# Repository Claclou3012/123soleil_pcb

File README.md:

# 1, 2, 3 Soleil — Version électronique

Réinterprétation électronique du jeu "1, 2, 3 Soleil" : trois stations équipées de capteurs de mouvement surveillent chaque joueur pendant la phase "Soleil" (silence), une LED RGB par joueur indique s'il est encore en jeu ou éliminé, le tout accompagné de musique et affiché sur un écran OLED.

## Principe du jeu

1. **Phase verte** : la musique joue, une LED au centre est allumée en vert, les joueurs peuvent avancer.
2. **Phase rouge** : la musique s'arrête, les 3 capteurs à ultrasons mesurent la distance de chaque joueur. Tout mouvement détecté élimine le joueur (sa LED passe au rouge).
3. Le cycle se répète jusqu'à ce qu'il ne reste plus qu'un joueur.

## Architecture électronique

```
Batterie LiPo ──> Verrouillage (S1 + Q2) ──> XIAO ESP32-S3
                                                   ├── Écran OLED (I2C) : round / joueurs restants
                                                   ├── Chaîne de 4 LED RGB adressables (3 joueurs + feu central)
                                                   ├── Haut-parleur (piloté par Q1) : musique / bruitages
                                                   └── 3x capteur HC-SR04 (Trig commun, Echo individuel avec pont diviseur)
```

### Points techniques clés
- **Double plan de masse** : une masse réelle (batterie, toujours active) et une masse commutée (périphériques, coupée par Q2 en veille), afin de permettre un allumage/extinction par simple pression sur un bouton, avec verrouillage électronique maintenu par le microcontrôleur.
- **Pont diviseur de tension** sur chaque ligne Echo, pour adapter le signal du HC-SR04 aux entrées 3,3V du XIAO.
- **Chaîne de LED adressables** pilotée depuis une seule broche du microcontrôleur.

## Liste des composants principaux

| Réf | Composant | Rôle |
|---|---|---|
| U1 | XIAO ESP32-S3 | Microcontrôleur |
| J1 | Écran OLED SSD1306 (I2C) | Affichage du jeu |
| U2, U3, U4 | HC-SR04 | Capteurs de mouvement (un par joueur) |
| D1-D3 | LED RGB adressable | Une par joueur |
| D4 | LED RGB adressable | Feu central (rouge/vert) |
| Q1 | NMOS | Pilotage du haut-parleur |
| Q2 | NMOS | Interrupteur à verrouillage (marche/arrêt) |
| S1 | Bouton poussoir | Marche / démarrage |
| LS1 | Haut-parleur | Musique et bruitages |
| J2 | Connecteur JST batterie | Alimentation LiPo |

La liste complète des composants (résistances, condensateurs, diodes) est disponible dans le fichier de schéma.

## Fichiers du projet

- `123Soleil.kicad_pro` — fichier projet KiCad
- `123Soleil.kicad_sch` — schéma électronique
- `123Soleil.kicad_pcb` — circuit imprimé (2 couches, plan de masse séparé sur chaque face)
- `ibom.html` 

## Images

### Schéma électronique

### PCB (vue 2D)

### Rendu 3D
### Recto

### Verso

## Fabrication et assemblage

- PCB 2 couches, plan de masse réelle en face arrière, plan de masse commutée en face avant.
- Plusieurs composants (XIAO, écran OLED, capteurs HC-SR04) sont montés sur supports de broches (sockets) plutôt que soudés directement, pour faciliter le remplacement.
- Point d'assemblage important : la broche VBAT du XIAO est une pastille sous le module, non accessible via les supports — un fil doit être soudé directement dessus avant d'enficher le module.

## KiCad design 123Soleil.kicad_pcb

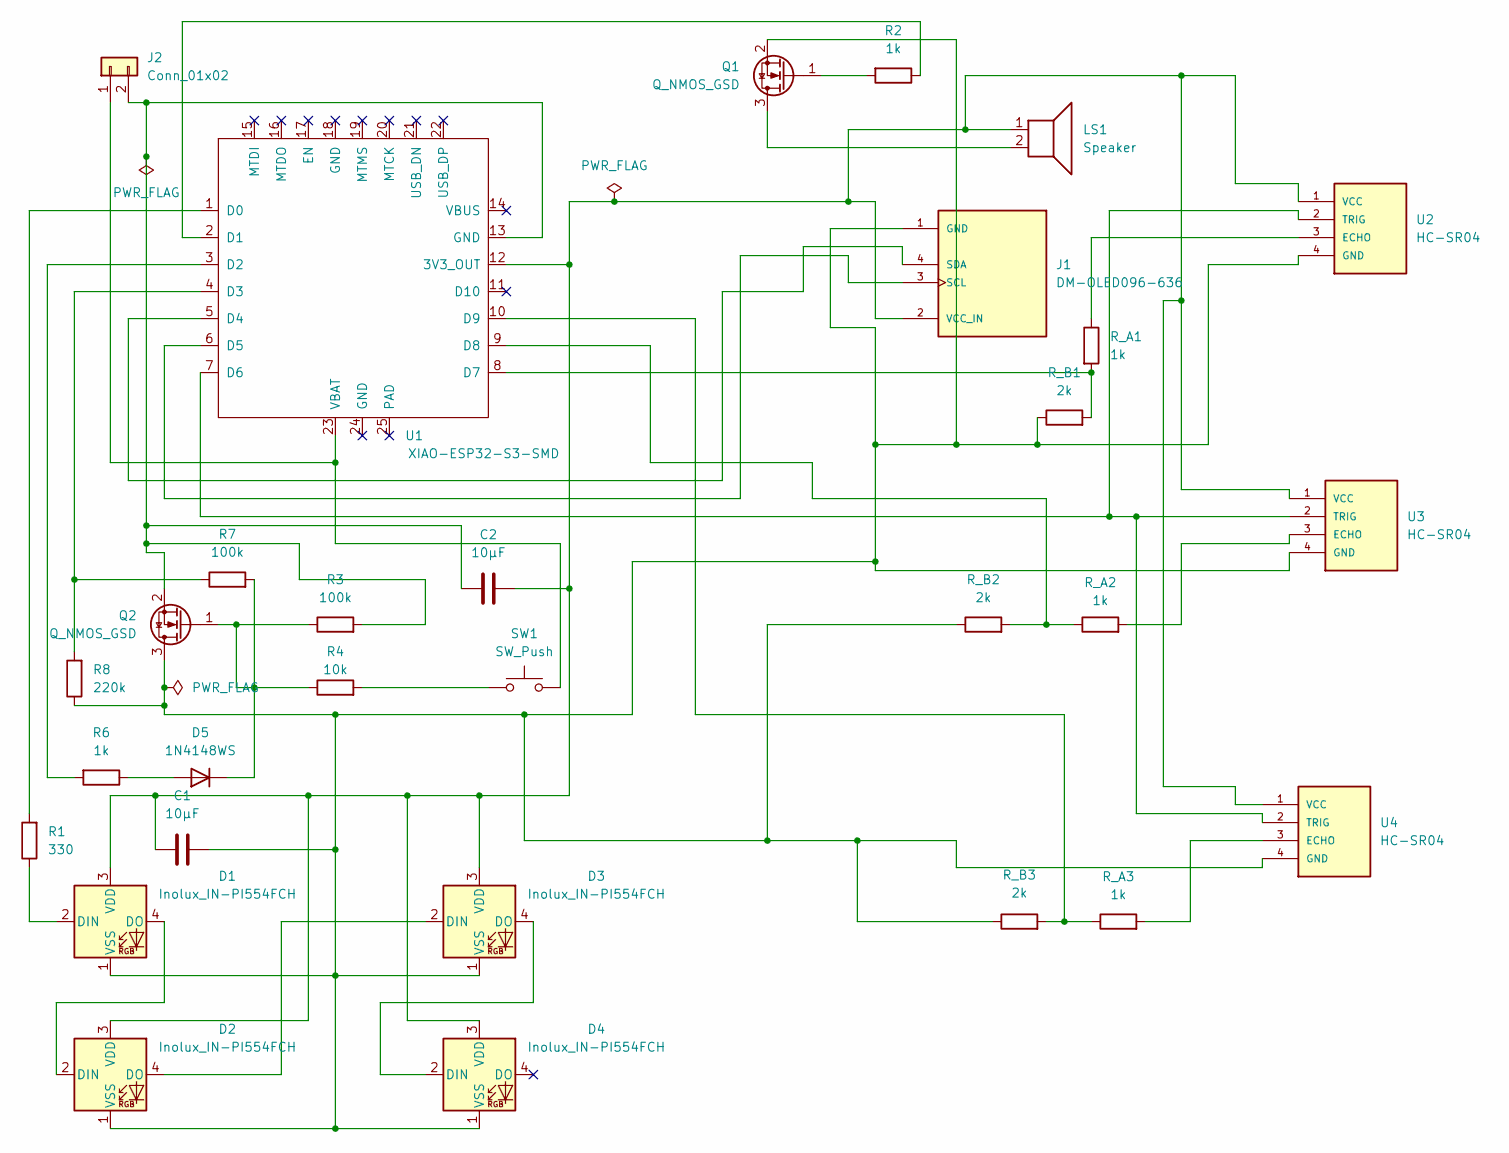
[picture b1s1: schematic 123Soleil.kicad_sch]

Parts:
C1, C2: 10µF; C_0805_2012Metric_Pad1.18x1.45mm_HandSolder
D1, D2, D3, D4: Inolux_IN-PI554FCH; LED_Inolux_IN-PI554FCH_PLCC4_5.0x5.0mm_P3.2mm
D5: 1N4148WS; D_SOD-323
J1: DM-OLED096-636; MODULE_DM-OLED096-636; PARTREV 2018-09-10
J2: Conn_01x02; JST_PH_S2B-PH-K_1x02_P2.00mm_Horizontal
LS1: Speaker; Speaker_CUI_CMR-1206S-67
Q1, Q2: Q_NMOS_GSD; SOT-23-3
R1: 330; R_0805_2012Metric_Pad1.20x1.40mm_HandSolder
R2, R6: 1k; R_0805_2012Metric_Pad1.20x1.40mm_HandSolder
R3, R7: 100k; R_0805_2012Metric_Pad1.20x1.40mm_HandSolder
R4: 10k; R_0805_2012Metric_Pad1.20x1.40mm_HandSolder
R8: 220k; R_0805_2012Metric_Pad1.20x1.40mm_HandSolder
R_A1, R_A2, R_A3: 1k; R_0805_2012Metric_Pad1.20x1.40mm_HandSolder
R_B1, R_B2, R_B3: 2k; R_0805_2012Metric_Pad1.20x1.40mm_HandSolder
SW1: SW_Push; SW_PUSH_6mm_H5mm
U1: XIAO-ESP32-S3-SMD
U2, U3, U4: HC-SR04; XCVR_HC-SR04

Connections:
unnamed: D1.2 (DIN), R1.1
unnamed: D1.4 (DO), D2.2 (DIN)
unnamed: C1.1, C2.2, D1.3 (VDD), D2.3 (VDD), D3.3 (VDD), D4.3 (VDD), J1.2 (VCC_IN), LS1.1, U1.12 (3V3_OUT), U2.1 (VCC), U3.1 (VCC), U4.1 (VCC)
unnamed: C1.2, D1.1 (VSS), D2.1 (VSS), D3.1 (VSS), D4.1 (VSS), J1.1 (GND), Q1.2 (S), Q2.3 (D), R8.1, R_B1.1, R_B2.1, R_B3.1, U2.4 (GND), U3.4 (GND), U4.4 (GND)
unnamed: D2.4 (DO), D3.2 (DIN)
unnamed: D3.4 (DO), D4.2 (DIN)
unnamed: D5.2 (A), R6.1
unnamed: D5.1 (K), Q2.1 (G), R3.1, R4.1, R7.2
unnamed: J1.3 (SCL), U1.6 (D5)
unnamed: J1.4 (SDA), U1.5 (D4)
unnamed: J2.1, SW1.2, U1.23 (VBAT)
unnamed: C2.1, J2.2, Q2.2 (S), R3.2, U1.13 (GND)
unnamed: LS1.2, Q1.3 (D)
unnamed: Q1.1 (G), R2.2
unnamed: R4.2, SW1.1
unnamed: R1.2, U1.1 (D0)
unnamed: R2.1, U1.2 (D1)
unnamed: R6.2, U1.3 (D2)
unnamed: R7.1, R8.2, U1.4 (D3)
unnamed: U1.7 (D6), U2.2 (TRIG), U3.2 (TRIG), U4.2 (TRIG)
unnamed: R_A1.2, R_B1.2, U1.8 (D7)
unnamed: R_A2.1, R_B2.2, U1.9 (D8)
unnamed: R_A3.1, R_B3.2, U1.10 (D9)
unnamed: R_A1.1, U2.3 (ECHO)
unnamed: R_A2.2, U3.3 (ECHO)
unnamed: R_A3.2, U4.3 (ECHO)

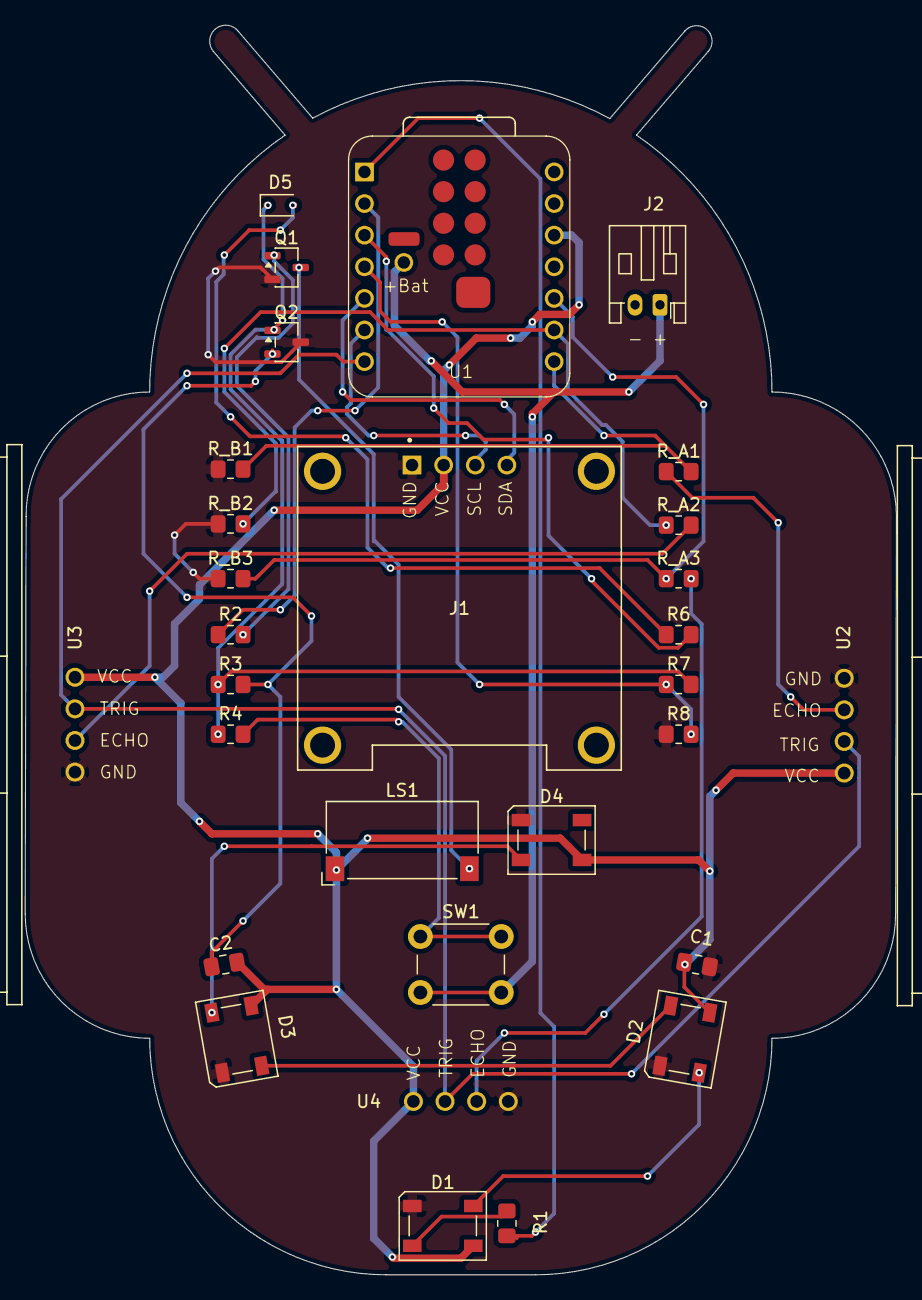
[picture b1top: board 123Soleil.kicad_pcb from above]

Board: 2 copper layers, 70.0 x 100.4 mm, 30 parts (0 on the bottom side), 26 nets.
